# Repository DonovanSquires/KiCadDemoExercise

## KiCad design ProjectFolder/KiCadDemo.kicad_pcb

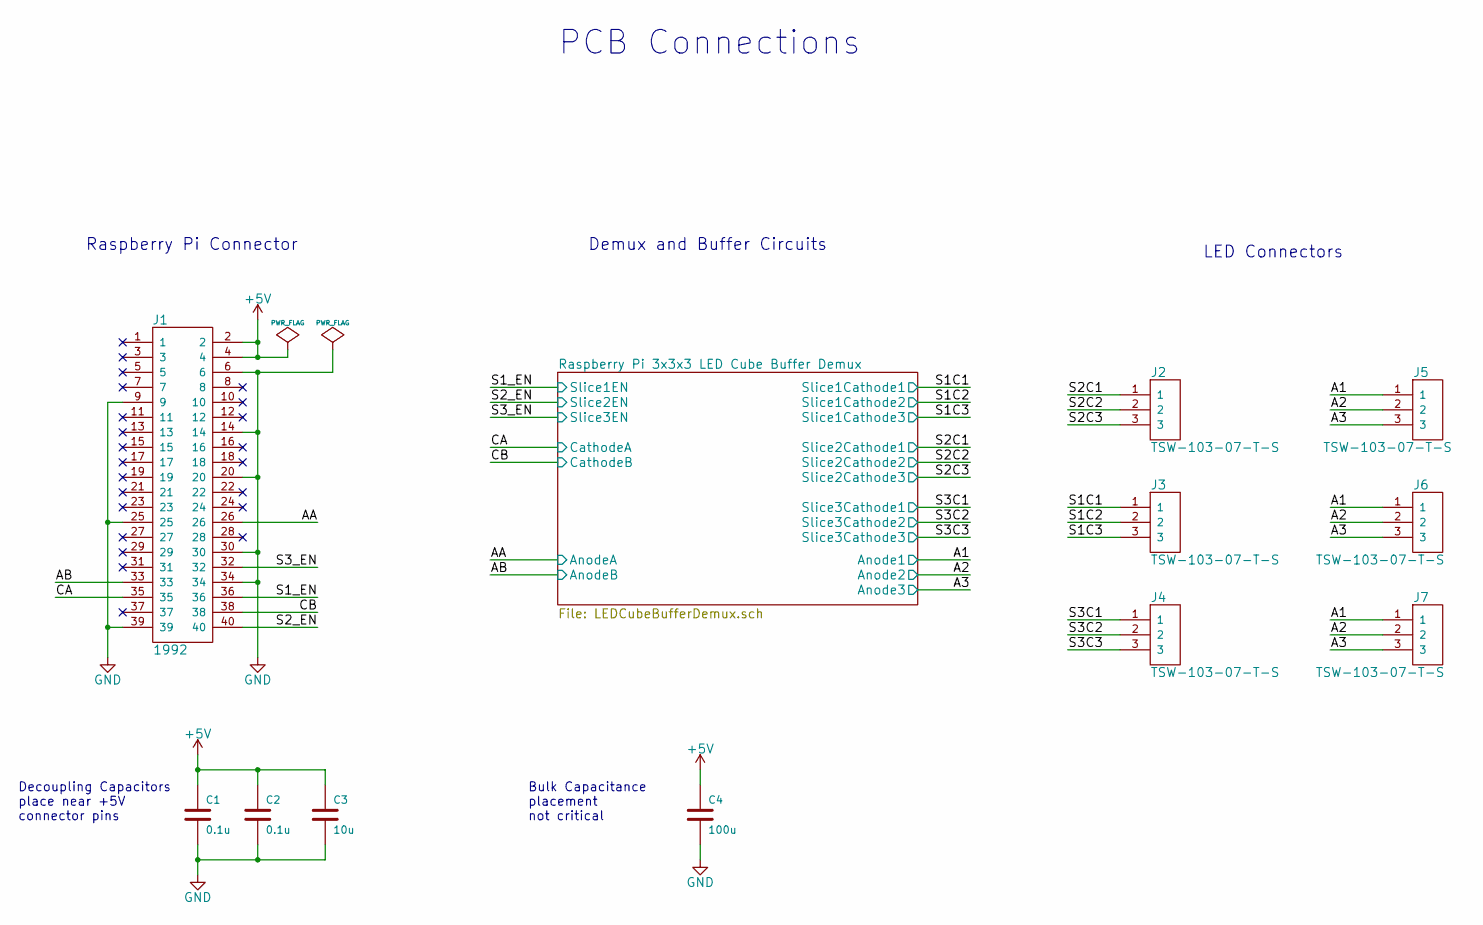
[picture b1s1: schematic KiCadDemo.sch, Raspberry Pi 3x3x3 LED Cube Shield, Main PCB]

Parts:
C1, C2: 0.1u; C_0805; Voltage 16V; Manufacturer Part Number C0805C104K4RACTU
C3: 10u; C_0805; Voltage 16V; Manufacturer Part Number GRM21BR61C106KE15L
C4: 100u; C_1210; Voltage 6.3V; Manufacturer Part Number GRM32ER60J107ME20L
J1: 1992; Manufacturer Part Number Unknown
J2, J3, J4, J5, J6, J7: TSW-103-07-T-S; tsw-103-07-t-s; Manufacturer Part Number TSW-103-07-T-S

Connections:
+5V: C1.1, C2.1, C3.1, C4.1, J1.2, J1.4; also elsewhere on the board
/Raspberry Pi 3x3x3 LED Cube Buffer Demux/Anode1: J5.1, J6.1, J7.1; also elsewhere on the board
/Raspberry Pi 3x3x3 LED Cube Buffer Demux/Anode2: J5.2, J6.2, J7.2; also elsewhere on the board
/Raspberry Pi 3x3x3 LED Cube Buffer Demux/Anode3: J5.3, J6.3, J7.3; also elsewhere on the board
/Raspberry Pi 3x3x3 LED Cube Buffer Demux/AnodeA: J1.26; also elsewhere on the board
/Raspberry Pi 3x3x3 LED Cube Buffer Demux/AnodeB: J1.33; also elsewhere on the board
/Raspberry Pi 3x3x3 LED Cube Buffer Demux/CathodeA: J1.35; also elsewhere on the board
/Raspberry Pi 3x3x3 LED Cube Buffer Demux/CathodeB: J1.38; also elsewhere on the board
/Raspberry Pi 3x3x3 LED Cube Buffer Demux/Slice1Cathode1: J3.1; also elsewhere on the board
/Raspberry Pi 3x3x3 LED Cube Buffer Demux/Slice1Cathode2: J3.2; also elsewhere on the board
/Raspberry Pi 3x3x3 LED Cube Buffer Demux/Slice1Cathode3: J3.3; also elsewhere on the board
/Raspberry Pi 3x3x3 LED Cube Buffer Demux/Slice1EN: J1.36; also elsewhere on the board
/Raspberry Pi 3x3x3 LED Cube Buffer Demux/Slice2Cathode1: J2.1; also elsewhere on the board
/Raspberry Pi 3x3x3 LED Cube Buffer Demux/Slice2Cathode2: J2.2; also elsewhere on the board
/Raspberry Pi 3x3x3 LED Cube Buffer Demux/Slice2Cathode3: J2.3; also elsewhere on the board
/Raspberry Pi 3x3x3 LED Cube Buffer Demux/Slice2EN: J1.40; also elsewhere on the board
/Raspberry Pi 3x3x3 LED Cube Buffer Demux/Slice3Cathode1: J4.1; also elsewhere on the board
/Raspberry Pi 3x3x3 LED Cube Buffer Demux/Slice3Cathode2: J4.2; also elsewhere on the board
/Raspberry Pi 3x3x3 LED Cube Buffer Demux/Slice3Cathode3: J4.3; also elsewhere on the board
/Raspberry Pi 3x3x3 LED Cube Buffer Demux/Slice3EN: J1.32; also elsewhere on the board
GND: C1.2, C2.2, C3.2, C4.2, J1.6, J1.9, J1.14, J1.20, J1.25, J1.30, J1.34, J1.39; also elsewhere on the board

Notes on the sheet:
Raspberry Pi Connector
Demux and Buffer Circuits
LED Connectors
PCB Connections
Decoupling Capacitors place near +5V connector pins
Bulk Capacitance placement not critical

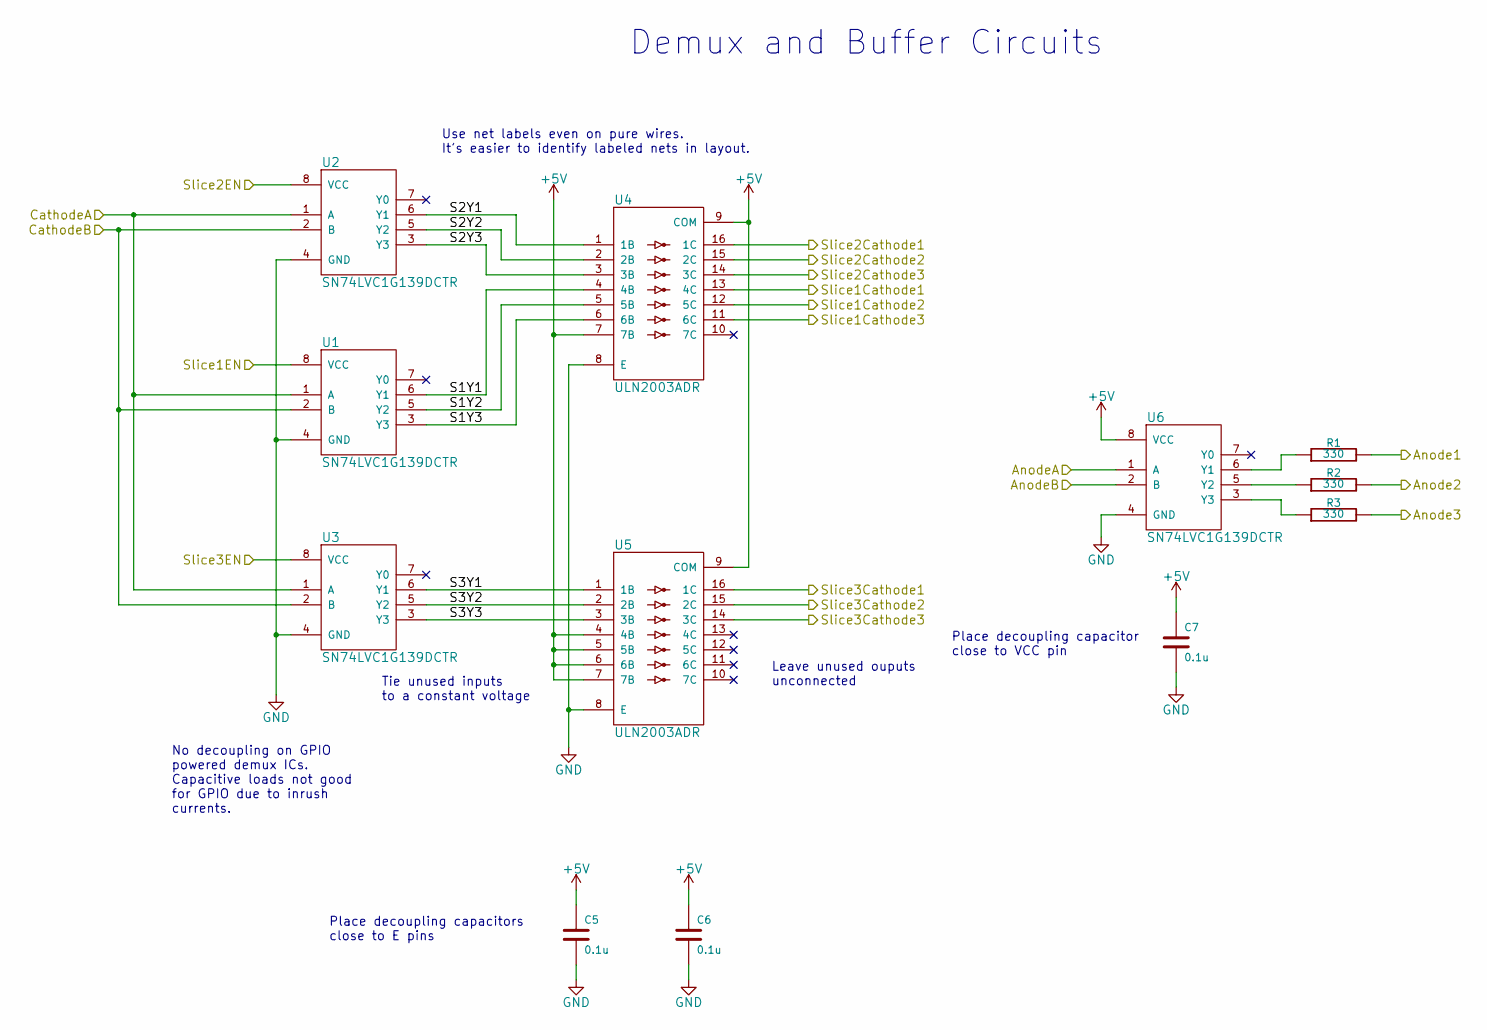
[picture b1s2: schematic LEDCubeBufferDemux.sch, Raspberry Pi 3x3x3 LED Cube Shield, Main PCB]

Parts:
C5, C6, C7: 0.1u; C_0805; Voltage 16V; Manufacturer Part Number C0805C104K4RACTU
R1, R2, R3: 330; R_0805; Tolerance 5%; Manufacturer Part Number ERJ-6GEYJ331V
U1, U2, U3, U6: SN74LVC1G139DCTR; sn74lvc1g139dctr; Manufacturer Part Number SN74LVC1G139DCTR
U4, U5: ULN2003ADR; Manufacturer Part Number ULN2003ADR

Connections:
+5V: C5.1, C6.1, C7.1, U4.7 (7B), U4.9 (COM), U5.4 (4B), U5.5 (5B), U5.6 (6B), U5.7 (7B), U5.9 (COM), U6.8 (VCC); also elsewhere on the board
/Raspberry Pi 3x3x3 LED Cube Buffer Demux/Anode1: R1.2; also elsewhere on the board
/Raspberry Pi 3x3x3 LED Cube Buffer Demux/Anode2: R2.2; also elsewhere on the board
/Raspberry Pi 3x3x3 LED Cube Buffer Demux/Anode3: R3.2; also elsewhere on the board
/Raspberry Pi 3x3x3 LED Cube Buffer Demux/AnodeA: U6.1 (A); also elsewhere on the board
/Raspberry Pi 3x3x3 LED Cube Buffer Demux/AnodeB: U6.2 (B); also elsewhere on the board
/Raspberry Pi 3x3x3 LED Cube Buffer Demux/CathodeA: U1.1 (A), U2.1 (A), U3.1 (A); also elsewhere on the board
/Raspberry Pi 3x3x3 LED Cube Buffer Demux/CathodeB: U1.2 (B), U2.2 (B), U3.2 (B); also elsewhere on the board
/Raspberry Pi 3x3x3 LED Cube Buffer Demux/S1Y1: U1.6 (Y1), U4.4 (4B)
/Raspberry Pi 3x3x3 LED Cube Buffer Demux/S1Y2: U1.5 (Y2), U4.5 (5B)
/Raspberry Pi 3x3x3 LED Cube Buffer Demux/S1Y3: U1.3 (Y3), U4.6 (6B)
/Raspberry Pi 3x3x3 LED Cube Buffer Demux/S2Y1: U2.6 (Y1), U4.1 (1B)
/Raspberry Pi 3x3x3 LED Cube Buffer Demux/S2Y2: U2.5 (Y2), U4.2 (2B)
/Raspberry Pi 3x3x3 LED Cube Buffer Demux/S2Y3: U2.3 (Y3), U4.3 (3B)
/Raspberry Pi 3x3x3 LED Cube Buffer Demux/S3Y1: U3.6 (Y1), U5.1 (1B)
/Raspberry Pi 3x3x3 LED Cube Buffer Demux/S3Y2: U3.5 (Y2), U5.2 (2B)
/Raspberry Pi 3x3x3 LED Cube Buffer Demux/S3Y3: U3.3 (Y3), U5.3 (3B)
/Raspberry Pi 3x3x3 LED Cube Buffer Demux/Slice1Cathode1: U4.13 (4C); also elsewhere on the board
/Raspberry Pi 3x3x3 LED Cube Buffer Demux/Slice1Cathode2: U4.12 (5C); also elsewhere on the board
/Raspberry Pi 3x3x3 LED Cube Buffer Demux/Slice1Cathode3: U4.11 (6C); also elsewhere on the board
/Raspberry Pi 3x3x3 LED Cube Buffer Demux/Slice1EN: U1.8 (VCC); also elsewhere on the board
/Raspberry Pi 3x3x3 LED Cube Buffer Demux/Slice2Cathode1: U4.16 (1C); also elsewhere on the board
/Raspberry Pi 3x3x3 LED Cube Buffer Demux/Slice2Cathode2: U4.15 (2C); also elsewhere on the board
/Raspberry Pi 3x3x3 LED Cube Buffer Demux/Slice2Cathode3: U4.14 (3C); also elsewhere on the board
/Raspberry Pi 3x3x3 LED Cube Buffer Demux/Slice2EN: U2.8 (VCC); also elsewhere on the board
/Raspberry Pi 3x3x3 LED Cube Buffer Demux/Slice3Cathode1: U5.16 (1C); also elsewhere on the board
/Raspberry Pi 3x3x3 LED Cube Buffer Demux/Slice3Cathode2: U5.15 (2C); also elsewhere on the board
/Raspberry Pi 3x3x3 LED Cube Buffer Demux/Slice3Cathode3: U5.14 (3C); also elsewhere on the board
/Raspberry Pi 3x3x3 LED Cube Buffer Demux/Slice3EN: U3.8 (VCC); also elsewhere on the board
GND: C5.2, C6.2, C7.2, U1.4 (GND), U2.4 (GND), U3.4 (GND), U4.8 (E), U5.8 (E), U6.4 (GND); also elsewhere on the board
unnamed: R1.1, U6.6 (Y1)
unnamed: R2.1, U6.5 (Y2)
unnamed: R3.1, U6.3 (Y3)

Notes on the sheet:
Demux and Buffer Circuits
Tie unused inputs to a constant voltage
Leave unused ouputs unconnected
Place decoupling capacitors close to E pins
Use net labels even on pure wires. It's easier to identify labeled nets in layout.
No decoupling on GPIO powered demux ICs. Capacitive loads not good for GPIO due to inrush currents.
Place decoupling capacitor close to VCC pin

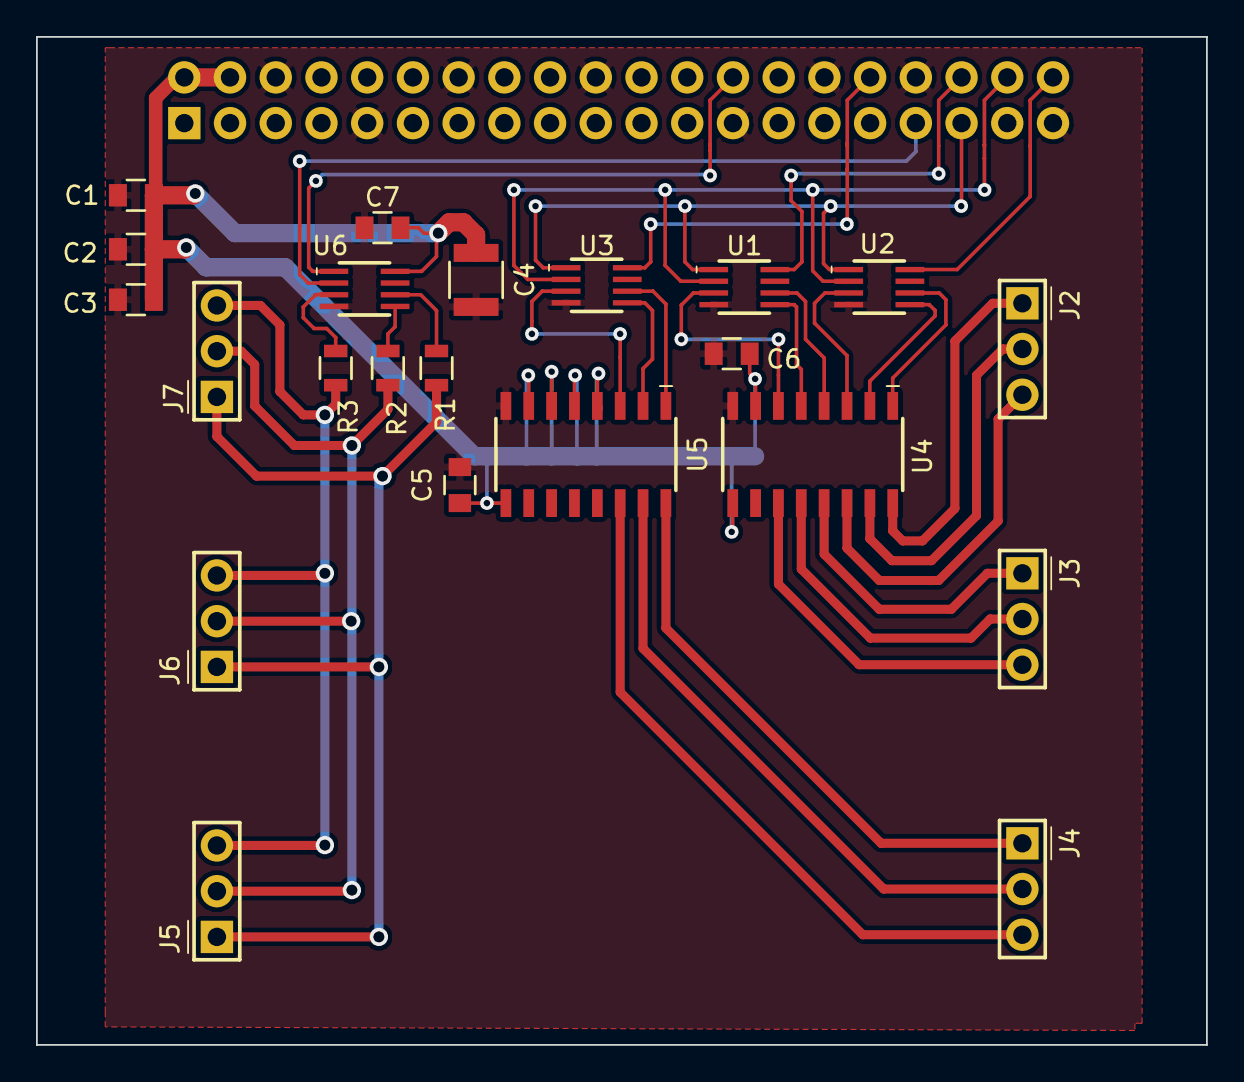
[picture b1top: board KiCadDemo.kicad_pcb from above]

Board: 2 copper layers, 65.0 x 56.0 mm, 24 parts (1 on the bottom side), 33 nets.

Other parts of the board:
raspberrypi2_shield: VAL**; raspberrypi2_shield

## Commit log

2015-03-18 Schematic, pcb libraries, and netlist created. Also, schematic creation documented with screenshots
2015-03-18 Changed LICENSE text to CC-BY 4.0
2015-03-19 Mostly finished PCB layout
2015-03-20 Added mounting holes, fixed Raspberry Pi reference footprint mounting hole locations, and removed inaccurate mechanical drawing
2015-03-20 branch to store exercise project, remove mounting holes including libraries
2015-03-20 Removed SchematicProcedure dir
2015-03-20 Added Excercise documents
2015-03-20 Updated table of contents and fixed typo in repository by creating a new one
2015-03-21 deleted inaccurate rpi print, updated system schematic

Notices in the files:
ProjectFolder/KiCadDemo.kicad_pcb:
License: CC-BY 4.0
